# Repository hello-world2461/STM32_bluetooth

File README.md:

Followed the following tutorials by Phil's labs (https://www.youtube.com/watch?v=nkHFoxe0mrU and https://www.youtube.com/watch?v=PlXd3lLZ4vc&t=0s) 
to practice PCB schematic and PCB layout design. Also might do some antenna design.

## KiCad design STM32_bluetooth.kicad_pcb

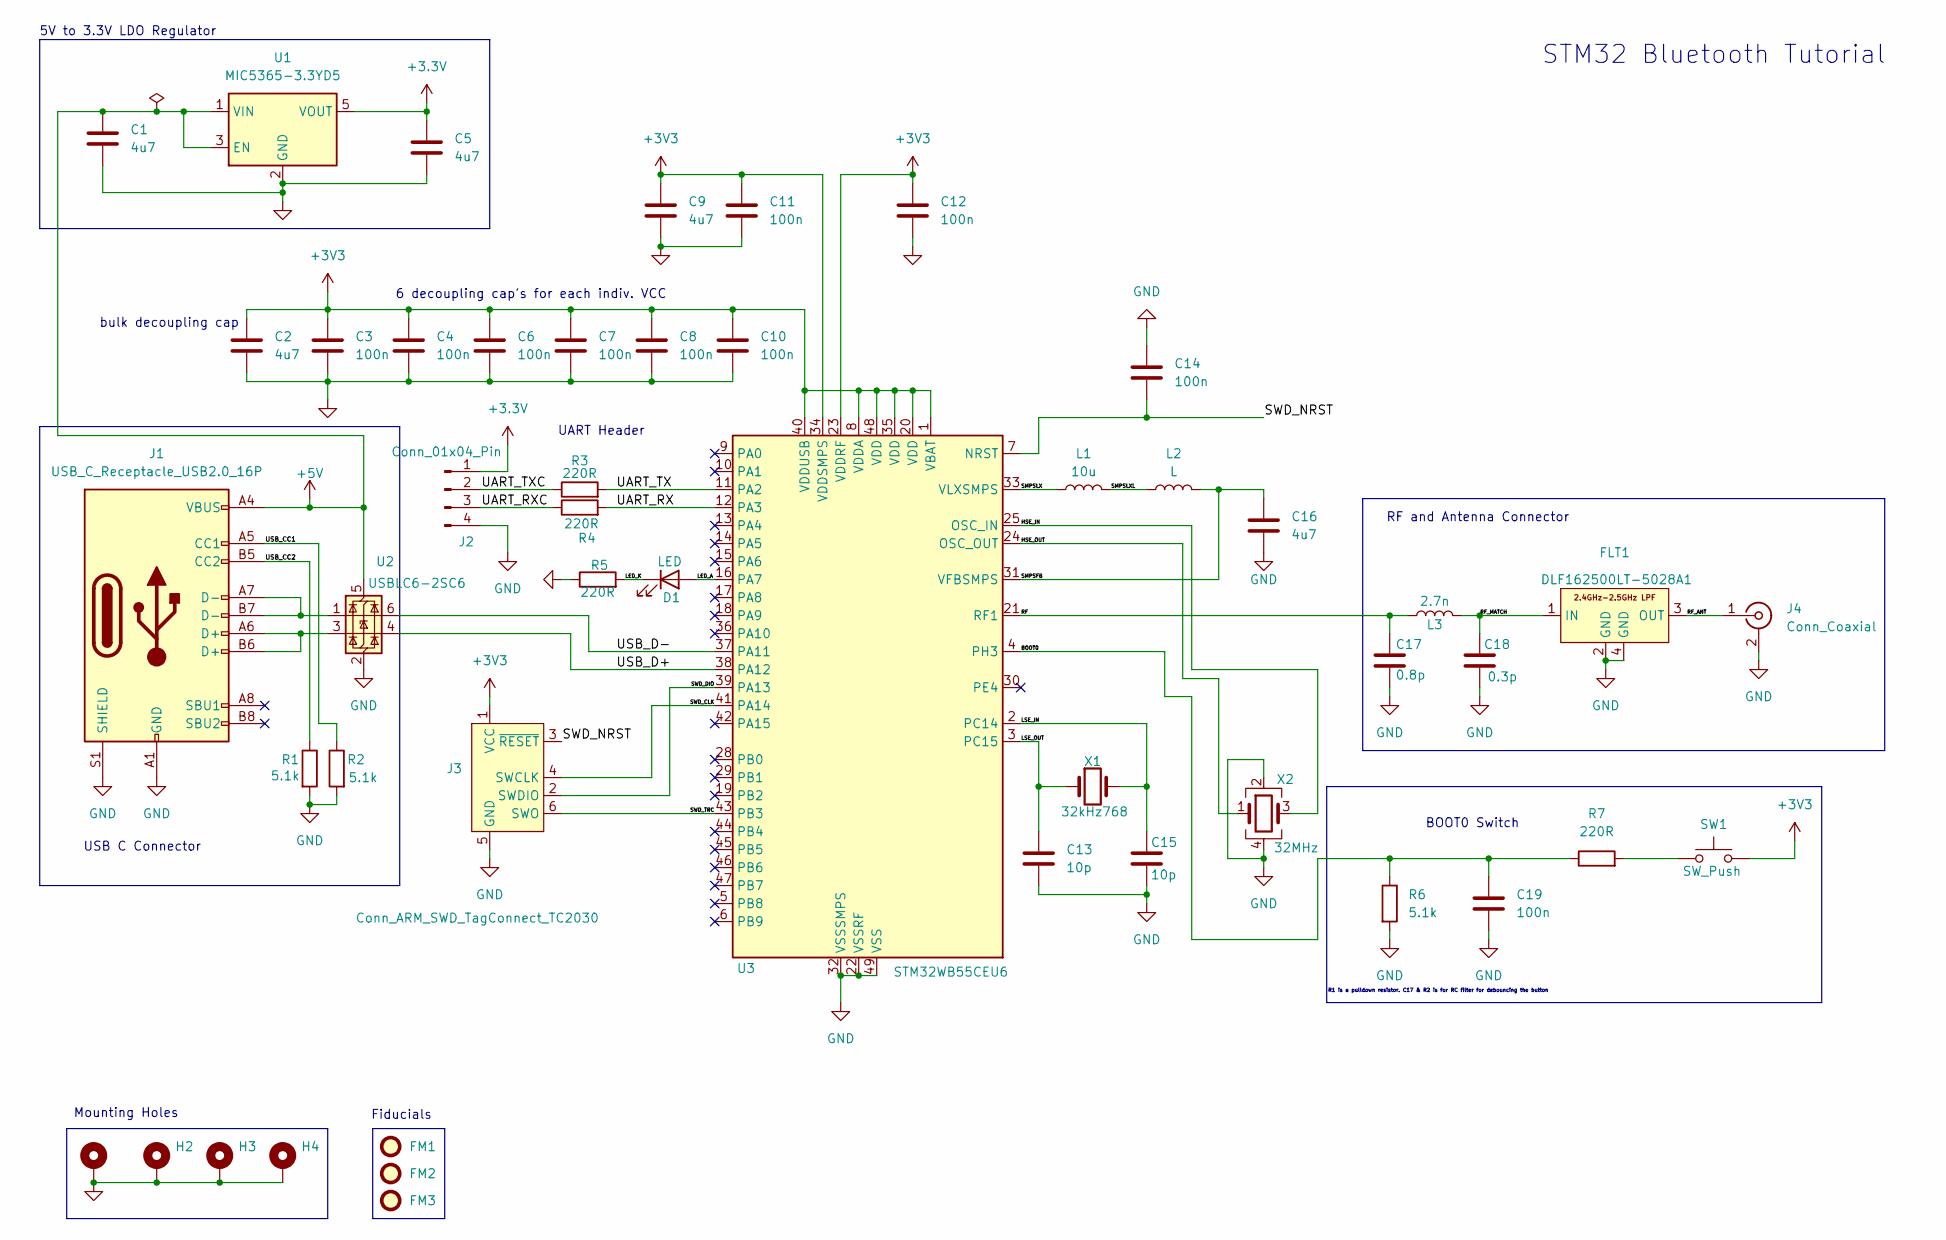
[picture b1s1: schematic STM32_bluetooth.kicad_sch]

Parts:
C1, C5: 4u7; C_0402_1005Metric
C2, C9, C16: 4u7; C_0603_1608Metric
C3, C4, C6, C7, C8, C10, C11, C12, C14, C19: 100n; C_0402_1005Metric
C13, C15: 10p; C_0402_1005Metric
C17: 0.8p; C_0402_1005Metric
C18: 0.3p; C_0402_1005Metric
D1: LED; LED_0402_1005Metric
FLT1: DLF162500LT-5028A1
FM1, FM2, FM3: Fiducial; Fiducial_1mm_Mask2mm
H1, H2, H3, H4: MountingHole_Pad; MountingHole_2.2mm_M2_Pad_Via
J1: USB_C_Receptacle_USB2.0_16P; USB_C_Receptacle_GCT_USB4105-xx-A_16P_TopMnt_Horizontal
J2: Conn_01x04_Pin; Molex_PicoBlade_53048-0410_1x04_P1.25mm_Horizontal
J3: Conn_ARM_SWD_TagConnect_TC2030; Tag-Connect_TC2030-IDC-FP_2x03_P1.27mm_Vertical
J4: Conn_Coaxial; U.FL_Hirose_U.FL-R-SMT-1_Vertical
L1: 10u; L_0402_1005Metric
L2: L; L_0805_2012Metric
L3: 2.7n; L_0402_1005Metric
R1, R2, R6: 5.1k; C_0402_1005Metric
R3, R4, R5, R7: 220R; C_0402_1005Metric
SW1: SW_Push; SW_SPST_CK_RS282G05A3
U1: MIC5365-3.3YD5; SOT-23-5
U2: USBLC6-2SC6; SOT-23-6
U3: STM32WB55CEU6; QFN-48-1EP_7x7mm_P0.5mm_EP5.6x5.6mm
X1: 32kHz768; Crystal_SMD_2012-2Pin_2.0x1.2mm
X2: 32MHz; Crystal_SMD_2016-4Pin_2.0x1.6mm

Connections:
+5V: C1.1, J1.A4 (VBUS), J1.A9 (VBUS), J1.B4 (VBUS), J1.B9 (VBUS), U1.1 (VIN), U1.3 (EN), U2.5 (VBUS)
/BOOT0: C19.1, R6.1, R7.1, U3.4 (PH3)
/HSE_IN: U3.25 (OSC_IN), X2.3
/HSE_OUT: U3.24 (OSC_OUT), X2.1
/LED_A: D1.2 (A), U3.16 (PA7)
/LED_K: D1.1 (K), R5.2
/LSE_IN: C15.1, U3.2 (PC14), X1.2
/LSE_OUT: C13.1, U3.3 (PC15), X1.1
/RF: C17.1, L3.1, U3.21 (RF1)
/RF_ANT: FLT1.3 (OUT), J4.1 (In)
/RF_MATCH: C18.1, FLT1.1 (IN), L3.2
/SMPSFB: C16.1, L2.2, U3.31 (VFBSMPS)
/SMPSLX: L1.1, U3.33 (VLXSMPS)
/SMPSLXL: L1.2, L2.1
/SWD_CLK: J3.4 (SWCLK), U3.41 (PA14)
/SWD_DIO: J3.2 (SWDIO), U3.39 (PA13)
/SWD_NRST: C14.2, J3.3 (~RESET), U3.7 (NRST)
/SWD_TRC: J3.6 (SWO), U3.43 (PB3)
/UART_RX: R4.2, U3.12 (PA3)
/UART_RXC: J2.3, R4.1
/UART_TX: R3.2, U3.11 (PA2)
/UART_TXC: J2.2, R3.1
/USB_CC1: J1.A5 (CC1), R2.1
/USB_CC2: J1.B5 (CC2), R1.1
/USB_D+: U2.4 (I/O2), U3.38 (PA12)
/USB_D-: U2.6 (I/O1), U3.37 (PA11)
GND: C1.2, C2.2, C3.2, C4.2, C5.2, C6.2, C7.2, C8.2, C9.2, C10.2, C11.2, C12.2, C13.2, C14.1, C15.2, C16.2, C17.2, C18.2, C19.2, FLT1.2 (GND), FLT1.4 (GND), H1.1, H2.1, H3.1, H4.1, J1.A1 (GND), J1.A12 (GND), J1.B1 (GND), J1.B12 (GND), J1.S1 (SHIELD), J2.4, J3.5 (GND), J4.2 (Ext), R1.2, R2.2, R5.1, R6.2, U1.2 (GND), U2.2 (GND), U3.22 (VSSRF), U3.32 (VSSSMPS), U3.49 (VSS), X2.2, X2.4
unnamed: J1.A6 (D+), J1.B6 (D+), U2.3 (I/O2)
unnamed: J1.A7 (D-), J1.B7 (D-), U2.1 (I/O1)
unnamed: R7.2, SW1.1

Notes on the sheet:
RF and Antenna Connector
Mounting Holes
5V to 3.3V LDO Regulator
R1 is a pulldown resistor. C17 & R2 is for RC filter for debouncing the button
USB C Connector
6 decoupling cap's for each indiv. VCC
Fiducials
BOOT0 Switch
bulk decoupling cap
UART Header
STM32 Bluetooth Tutorial

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
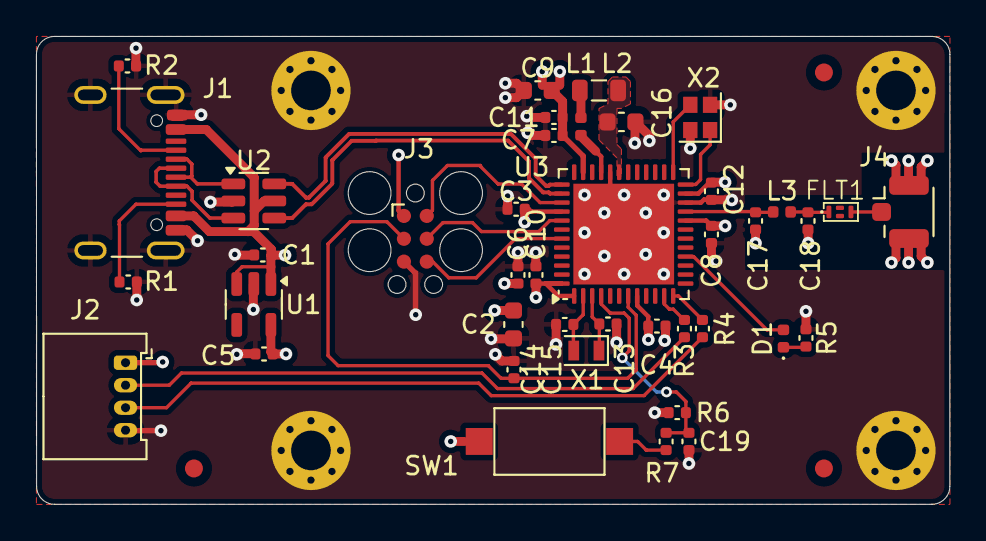
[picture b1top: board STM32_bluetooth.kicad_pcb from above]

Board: 4 copper layers, 50.8 x 26.0 mm, 48 parts (0 on the bottom side), 32 nets.

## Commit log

2025-01-26 Created schematic circuit. Still need to add footprints for all components.
2025-02-03 Added all footprints
2025-02-03 defined some pcb rules for traces, layers, etc
2025-02-04 started pcb layout.
2025-02-05 board layout completed
2025-02-07 Added via's and tracing for RF circuit.
2025-02-09 finished via's, finished tracing, still need to connect ground pins.
2025-02-10 finished the layout, the connections, silkscreen.
2025-02-10 placed origin
